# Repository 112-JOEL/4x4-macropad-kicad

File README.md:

# 4x4 Macropad - KiCad Project

A 4x4 programmable mechanical macropad designed using KiCad. This project includes the full schematic and PCB layout.

## 📁 Files Included
- `Macropad 4X4 schematics.kicad_sch` – Schematic file
- `Macropad 4X4 pcb.kicad_pcb` – PCB layout
- `keyboard-layout.json` – Optional layout info

## 🛠️ Tools Used
- [KiCad](https://kicad.org/) (v6 or v7)

## 📄 License
This project is licensed under the [MIT License](LICENSE).

## 🙋‍♂️ Author
Joel Paul Laiju

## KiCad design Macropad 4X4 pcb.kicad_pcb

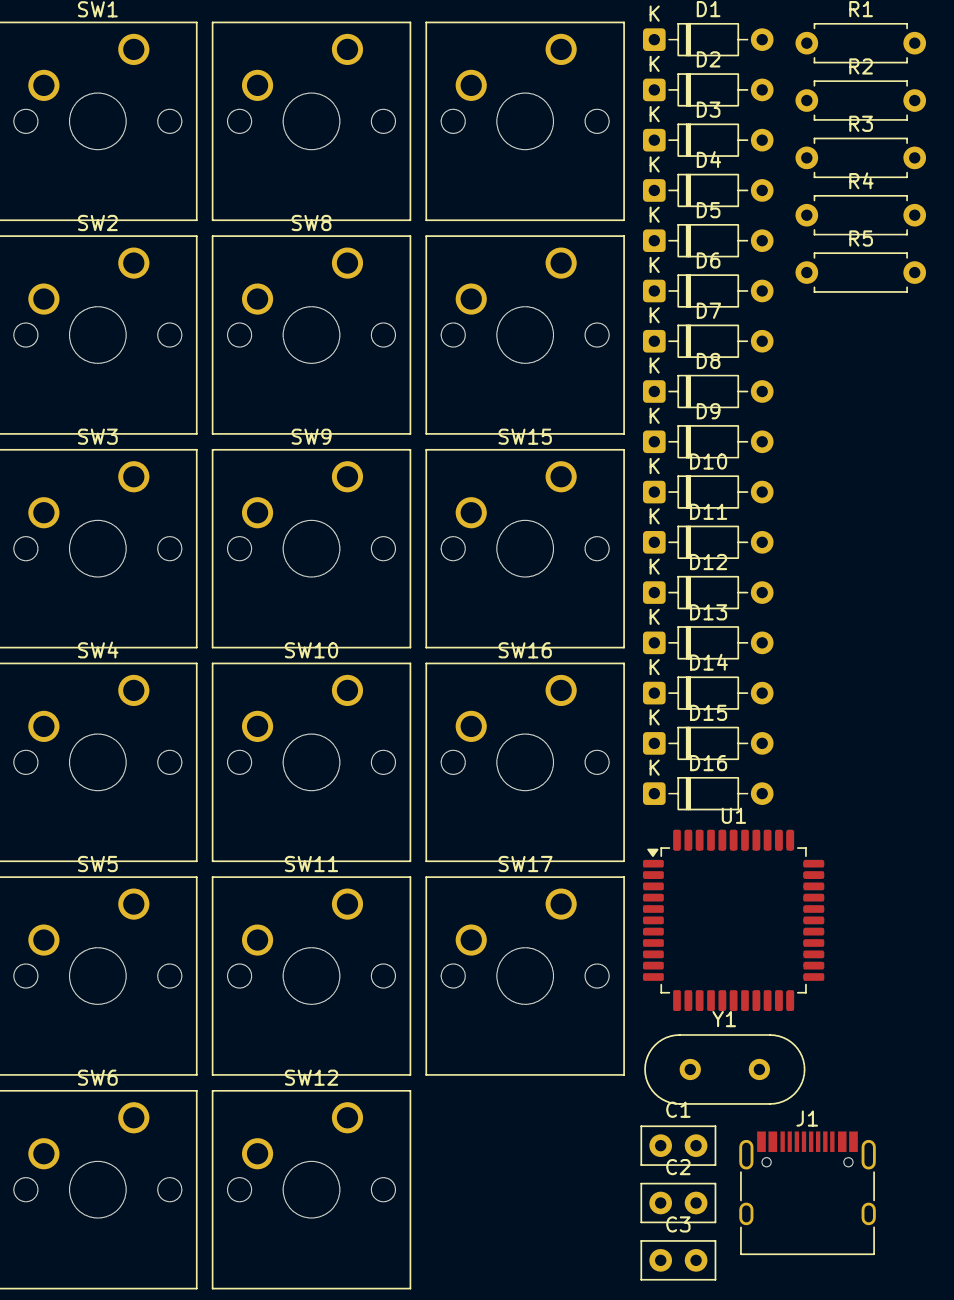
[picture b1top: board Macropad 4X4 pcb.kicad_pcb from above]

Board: 2 copper layers, 44 parts (0 on the bottom side), 36 nets, no tracks yet.

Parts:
C1, C2, C3: C; C_Disc_D5.0mm_W2.5mm_P2.50mm
D1, D2, D3, D4, D5, D6, D7, D8, D9, D10, D11, D12, D13, D14, D15, D16: D; D_DO-35_SOD27_P7.62mm_Horizontal
J1: USB_C_Receptacle_USB2.0_16P; USB_C_Receptacle_HRO_TYPE-C-31-M-12
R1, R2, R3, R4, R5: R; R_Axial_DIN0207_L6.3mm_D2.5mm_P7.62mm_Horizontal
SW1, SW2, SW3, SW4, SW5, SW6, SW7, SW8, SW9, SW10, SW11, SW12, SW13, SW14, SW15, SW16, SW17: SW_Push; SW_Cherry_MX_1.00u_PCB
U1: ATmega32U4-A; TQFP-44_10x10mm_P0.8mm
Y1: Crystal_GND23_Small; Crystal_HC49-4H_Vertical

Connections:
+5V: J1.A4 (VBUS), J1.A9 (VBUS), J1.B4 (VBUS), J1.B9 (VBUS), R5.1, U1.2 (UVCC), U1.7 (VBUS), U1.14 (VCC), U1.24 (AVCC), U1.34 (VCC), U1.44 (AVCC)
COLUMN 1: SW2.1, SW3.1, SW4.1, SW5.1, U1.8 (PB0)
COLUMN 2: SW6.1, SW7.1, SW8.1, SW9.1, U1.9 (PB1)
COLUMN 3: SW10.1, SW11.1, SW12.1, SW13.1, U1.10 (PB2)
COLUMN 4: SW14.1, SW15.1, SW16.1, SW17.1, U1.11 (PB3)
D+: J1.A6 (D+), J1.B6 (D+), R4.1
D-: J1.A7 (D-), J1.B7 (D-), R3.1
GND: C1.1, C2.1, C3.2, J1.A1 (GND), J1.A12 (GND), J1.B1 (GND), J1.B12 (GND), J1.S1 (SHIELD), R1.2, R2.1, SW1.1, U1.5 (UGND), U1.15 (GND), U1.23 (GND), U1.35 (GND), U1.43 (GND), Y1.2
unnamed: D1.1 (K), SW2.2
unnamed: D2.1 (K), SW3.2
unnamed: D3.1 (K), SW4.2
unnamed: D4.1 (K), SW5.2
unnamed: D5.1 (K), SW6.2
unnamed: D6.1 (K), SW7.2
unnamed: D7.1 (K), SW8.2
unnamed: D8.1 (K), SW9.2
unnamed: D9.1 (K), SW10.2
unnamed: D10.1 (K), SW11.2
unnamed: D11.1 (K), SW12.2
unnamed: D12.1 (K), SW13.2
unnamed: D13.1 (K), SW14.2
unnamed: D14.1 (K), SW15.2
unnamed: D15.1 (K), SW16.2
unnamed: D16.1 (K), SW17.2
unnamed: J1.A5 (CC1), R1.1
unnamed: J1.B5 (CC2), R2.2
unnamed: R4.2, U1.4 (D+)
unnamed: R3.2, U1.3 (D-)
unnamed: C3.1, U1.6 (UCAP)
unnamed: C1.2, U1.17 (XTAL1)
unnamed: C2.2, U1.16 (XTAL2), Y1.1
unnamed: R5.2, SW1.2, U1.13 (~RESET)
ROW 1: D4.2 (A), D8.2 (A), D12.2 (A), D16.2 (A), U1.18 (PD0)
ROW 2: D1.2 (A), D5.2 (A), D9.2 (A), D13.2 (A), U1.19 (PD1)
ROW 3: D2.2 (A), D6.2 (A), D10.2 (A), D14.2 (A), U1.20 (PD2)
ROW 4: D3.2 (A), D7.2 (A), D11.2 (A), D15.2 (A), U1.21 (PD3)

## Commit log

2025-06-13 Add files via upload
    Upload KiCad schematic and PCB for 4x4 macropad
2025-06-13 Create LICENSE
    Add MIT License
